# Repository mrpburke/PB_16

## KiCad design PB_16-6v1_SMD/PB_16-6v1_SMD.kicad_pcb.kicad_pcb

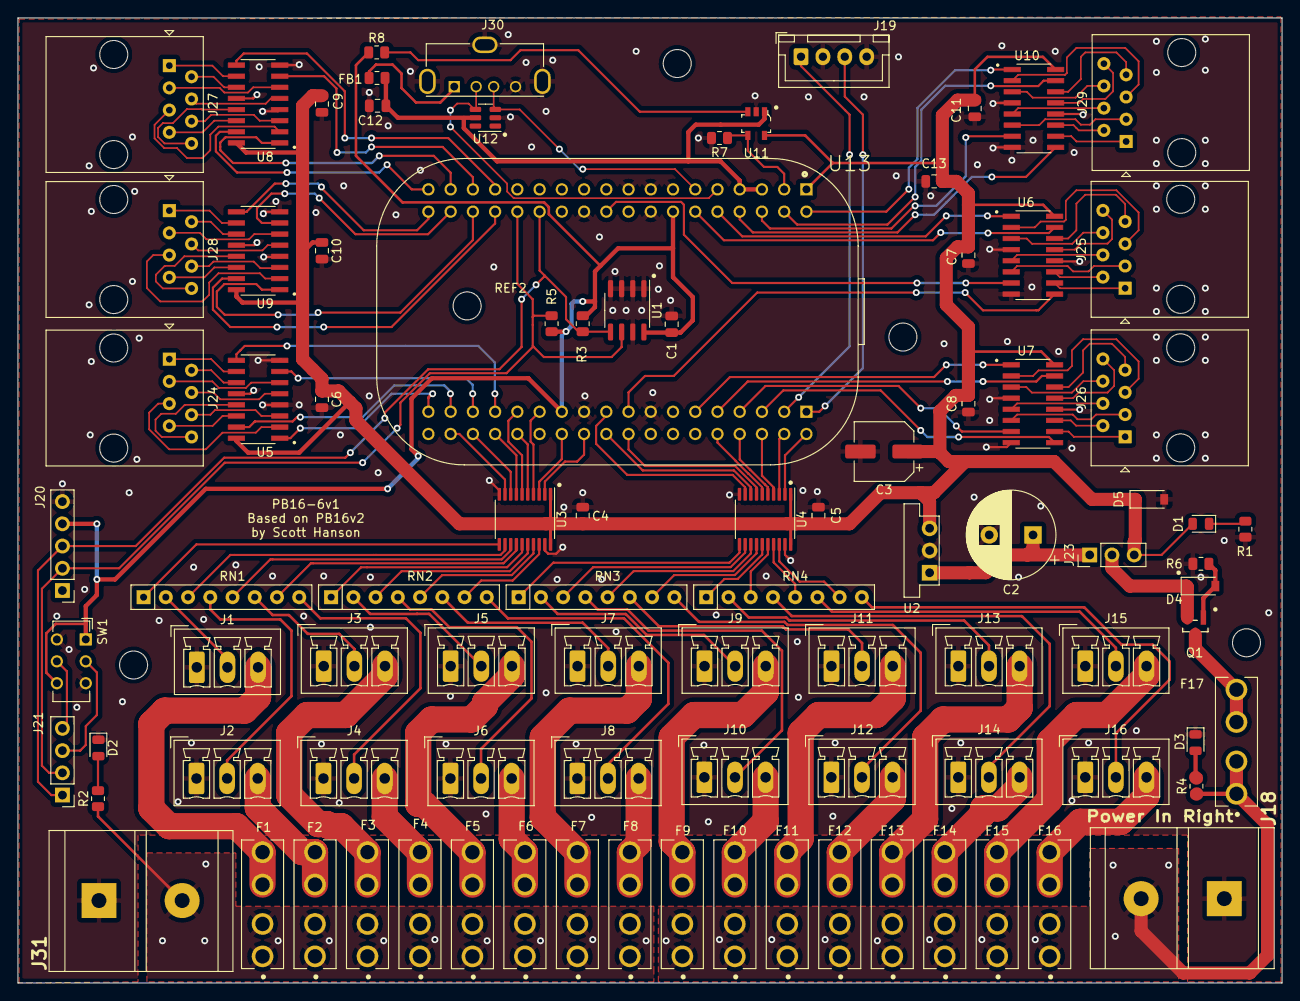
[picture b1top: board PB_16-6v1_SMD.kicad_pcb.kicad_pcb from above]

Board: 2 copper layers, 144.4 x 110.2 mm, 97 parts (0 on the bottom side), 160 nets.

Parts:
C1, C4, C5, C6, C7, C8, C9, C10, C11, C12, C13: 0.1uF; C_0805_2012Metric
C2: 220uF; CP_Radial_D10.0mm_P5.00mm
C3: 100uF; CP_Elec_6.3x5.4_Nichicon
D1: 5V LED; LED_0805_2012Metric
D2: VIN1 LED; LED_0805_2012Metric
D3: VIN2; LED_0805_2012Metric
D4: Zener 10V; D_SOD-123
D5: Zener 5.1V; D_SOD-123
F1, F2, F3, F4, F5, F6, F7, F8, F9, F10, F11, F12, F13, F14, F15, F16, F17: 3544-2; FUSE_3544-2
FB1: 150 OHM; R_0805_2012Metric
J1, J2, J3, J4, J5, J6, J7, J8, J9, J10, J11, J12, J13, J14, J15, J16: PhoenixContact_MCV_1,5_3-G-3.5_1x03_P3.50mm_Vertical
J18: Power In Right; BARRIER_BLOCK_1ROW_2POS_P9.5MM
J19: GPIO Header; JST_XH_B4B-XH-A_1x04_P2.50mm_Vertical
J20: RTC Conn; PinHeader_1x05_P2.54mm_Vertical
J21: OLED Conn; PinHeader_1x04_P2.54mm_Vertical
J23: VIN Voltage; PinHeader_1x03_P2.54mm_Vertical
J24, J25, J26, J27, J28, J29: RJ45; RJ45_Amphenol_54602-x08_Horizontal
J30: USB_A; USB_A_Molex_105057_Vertical
J31: Power In Left; BARRIER_BLOCK_1ROW_2POS_P9.5MM
Q1: DMP3056L-7; Diodes_Inc.-SOT23-01_2017-0-IPC_A
R1: 120; R_0805_2012Metric
R2, R4: 1K; R_0805_2012Metric
R3, R5: 4.7k; R_0805_2012Metric
R6: 100K; R_0805_2012Metric
R7, R8: 10K; R_0805_2012Metric
REF1, REF2, REF3, REF4, REF5: MountingHole_3.2mm_M3
RN1, RN2, RN3, RN4: 33; R_Array_SIP8
SW1: OLED Select; SW_CuK_JS202011CQN_DPDT_Straight
U1: AT24C256C-SSGL-T; SOIC-8_3.9x4.9mm_P1.27mm
U2: OKI-78SR-5_1.5-W36-C; Converter_DCDC_Murata_OKI-78SR_Vertical
U3, U4: SN74HCT245PWR; TSSOP-20_4.4x6.5mm_P0.65mm
U5, U6, U7, U8, U9, U10: AM26C31IDR; SOIC127P600X175-16N
U11: TPS2051BDBVR; SOT-753
U12: TPD4S009DBVR; SOT-23-6
U13: POCKETBEAGLE-SC-569; BEAGLE_POCKETBEAGLE-SC-569

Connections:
+3V3: C1.2, J20.4, R3.1, R5.1, R8.1, SW1.1 (A), SW1.6 (C), U1.8 (VCC), U13.P1_14 (SYS_3.3V), U13.P2_23 (SYS_3.3V)
+5V: C3.1, C4.1, C5.1, C6.1, C7.1, C8.1, C9.1, C10.1, C11.1, C13.1, D1.2 (A), D5.1 (K), J23.3, U2.3 (OUT), U3.1 (DIR), U3.20 (VCC), U4.1 (DIR), U4.20 (VCC), U5.16 (VCC), U6.16 (VCC), U7.16 (VCC), U8.16 (VCC), U9.16 (VCC), U10.16 (VCC), U11.5 (IN), U13.P1_1 (SYS_VIN)
/OLED_Pin_3: J21.3, SW1.2 (B)
/OLED_Pin_4: J21.4, SW1.5 (B)
/Output 1 - 8/DOUT1: J1.2, RN1.2 (R1.2)
/Output 1 - 8/DOUT2: J2.2, RN1.4 (R2.2)
/Output 1 - 8/DOUT3: J3.2, RN1.6 (R3.2)
/Output 1 - 8/DOUT4: J4.2, RN1.8 (R4.2)
/Output 1 - 8/DOUT5: J5.2, RN2.2 (R1.2)
/Output 1 - 8/DOUT6: J6.2, RN2.4 (R2.2)
/Output 1 - 8/DOUT7: J7.2, RN2.6 (R3.2)
/Output 1 - 8/DOUT8: J8.2, RN2.8 (R4.2)
/Output 1 - 8/VOUT1: F1.2_1, F1.2_2, J1.3
/Output 1 - 8/VOUT2: F2.2_1, F2.2_2, J2.3
/Output 1 - 8/VOUT3: F3.2_1, F3.2_2, J3.3
/Output 1 - 8/VOUT4: F4.2_1, F4.2_2, J4.3
/Output 1 - 8/VOUT5: F5.2_1, F5.2_2, J5.3
/Output 1 - 8/VOUT6: F6.2_1, F6.2_2, J6.3
/Output 1 - 8/VOUT7: F7.2_1, F7.2_2, J7.3
/Output 1 - 8/VOUT8: F8.2_1, F8.2_2, J8.3
/Output 9 - 16/DOUT9: J9.2, RN3.2 (R1.2)
/Output 9 - 16/DOUT10: J10.2, RN3.4 (R2.2)
/Output 9 - 16/DOUT11: J11.2, RN3.6 (R3.2)
/Output 9 - 16/DOUT12: J12.2, RN3.8 (R4.2)
/Output 9 - 16/DOUT13: J13.2, RN4.2 (R1.2)
/Output 9 - 16/DOUT14: J14.2, RN4.4 (R2.2)
/Output 9 - 16/DOUT15: J15.2, RN4.6 (R3.2)
/Output 9 - 16/DOUT16: J16.2, RN4.8 (R4.2)
/Output 9 - 16/VOUT9: F9.2_1, F9.2_2, J9.3
/Output 9 - 16/VOUT10: F10.2_1, F10.2_2, J10.3
/Output 9 - 16/VOUT11: F11.2_1, F11.2_2, J11.3
/Output 9 - 16/VOUT12: F12.2_1, F12.2_2, J12.3
/Output 9 - 16/VOUT13: F13.2_1, F13.2_2, J13.3
/Output 9 - 16/VOUT14: F14.2_1, F14.2_2, J14.3
/Output 9 - 16/VOUT15: F15.2_1, F15.2_2, J15.3
/Output 9 - 16/VOUT16: F16.2_1, F16.2_2, J16.3
/USB/V_USB_FB: FB1.2, J30.1 (VBUS)
/VIN_FUSE: F17.2_1, F17.2_2, Q1.3 (D)
DATA1: U3.9 (A8), U13.P2_34 (PRU0_5)
DATA2: U3.8 (A7), U13.P2_32 (PRU0_2)
DATA3: U3.7 (A6), U13.P2_30 (PRU0_3)
DATA4: U3.6 (A5), U13.P2_27 (SPI1_MISO)
DATA5: U3.5 (A4), U13.P2_28 (PRU0_6)
DATA6: U3.4 (A3), U13.P2_25 (SPI1_MOSI)
DATA7: U3.3 (A2), U13.P2_24 (GPIO_48)
DATA8: U3.2 (A1), U13.P2_22 (GPIO_46)
DATA9: U4.9 (A8), U13.P2_19 (GPIO_27)
DATA10: U4.8 (A7), U13.P2_20 (GPIO_64)
DATA11: U4.7 (A6), U13.P2_18 (GPIO_47)
DATA12: U4.6 (A5), U13.P2_10 (GPIO_52)
DATA13: U4.5 (A4), U13.P2_8 (GPIO_60)
DATA14: U4.4 (A3), U13.P2_6 (GPIO_57)
DATA15: U4.3 (A2), U13.P2_4 (GPIO_58)
DATA16: U4.2 (A1), U13.P2_2 (GPIO_59)
GND: C1.1, C2.2, C3.2, C4.2, C5.2, C6.2, C7.2, C8.2, C9.2, C10.2, C11.2, C12.2, C13.2, D2.1 (K), D3.1 (K), D5.2 (A), J1.1, J2.1, J3.1, J4.1, J5.1, J6.1, J7.1, J8.1, J9.1, J10.1, J11.1, J12.1, J13.1, J14.1, J15.1, J16.1, J18.1, J19.2, J19.4, J20.5, J30.4 (GND), J30.5 (Shield), J31.1, R1.2, R6.2, R7.2, SW1.3 (C), SW1.4 (A), U1.1 (A0), U1.2 (A1), U1.3 (A2), U1.4 (GND), U1.7 (WP), U2.2 (GND), U3.10 (GND), U3.19 (~OE), U4.10 (GND), U4.19 (~OE), U5.4 (G), U5.8 (GND), U5.12 (~G), U6.4 (G), U6.8 (GND), U6.12 (~G), U7.4 (G), U7.8 (GND), U7.12 (~G), U8.4 (G), U8.8 (GND), U8.12 (~G), U9.4 (G), U9.8 (GND), U9.12 (~G), U10.4 (G), U10.8 (GND), U10.12 (~G), U11.2 (GND), U12.2 (GND), U13.P1_13 (USB1_ID), U13.P1_15 (USB1_GND), U13.P1_16 (SYS_GND), U13.P1_17 (AIN1.8V_REF-), U13.P1_22 (SYS_GND), U13.P2_15 (SYS_GND), U13.P2_21 (SYS_GND)
GPIO1: J19.1, U13.P2_3 (GPIO_23)
GPIO2: J19.3, U13.P2_1 (PWM1_A)
I2C_SCL: J20.2, J21.2, R5.2, U1.6 (SCL), U13.P1_28 (I2C2_SCL)
I2C_SDA: J20.3, J21.1, R3.2, U1.5 (SDA), U13.P1_26 (I2C2_SDA)
unnamed: C2.1, J23.1, U2.1 (IN)
unnamed: D1.1 (K), R1.1
unnamed: D2.2 (A), R2.2
unnamed: D3.2 (A), R4.2
unnamed: D4.2 (A), Q1.1 (G), R6.1
unnamed: R8.2, U11.3 (~OC)
unnamed: RN1.1 (R1.1), U3.11 (B8)
unnamed: RN1.3 (R2.1), U3.12 (B7)
unnamed: RN1.5 (R3.1), U3.13 (B6)
unnamed: RN1.7 (R4.1), U3.14 (B5)
unnamed: RN2.1 (R1.1), U3.15 (B4)
unnamed: RN2.3 (R2.1), U3.16 (B3)
unnamed: RN2.5 (R3.1), U3.17 (B2)
unnamed: RN2.7 (R4.1), U3.18 (B1)
unnamed: RN3.1 (R1.1), U4.11 (B8)
unnamed: RN3.3 (R2.1), U4.12 (B7)
unnamed: RN3.5 (R3.1), U4.13 (B6)
unnamed: RN3.7 (R4.1), U4.14 (B5)
unnamed: RN4.1 (R1.1), U4.15 (B4)
unnamed: RN4.3 (R2.1), U4.16 (B3)
unnamed: RN4.5 (R3.1), U4.17 (B2)
unnamed: RN4.7 (R4.1), U4.18 (B1)
OUT17: U7.9 (3A), U13.P2_5 (UART4_RX)
OUT17+: J26.1, U7.10 (3Y)
OUT17-: J26.2, U7.11 (3Z)
OUT18: U7.7 (2A), U13.P2_7 (UART4_TX)
OUT18+: J26.3, U7.6 (2Y)
OUT18-: J26.4, U7.5 (2Z)
OUT19: U7.1 (1A), U13.P2_11 (I2C1_SDA)
OUT19+: J26.5, U7.2 (1Y)
OUT19-: J26.6, U7.3 (1Z)
OUT20: U7.15 (4A), U13.P2_9 (I2C1_SCL)
OUT20+: J26.7, U7.14 (4Y)
OUT20-: J26.8, U7.13 (4Z)
OUT21: U5.9 (3A), U13.P2_29 (SPI1_CLK)
OUT21+: J24.1, U5.10 (3Y)
OUT21-: J24.2, U5.11 (3Z)
OUT22: U5.7 (2A), U13.P2_31 (SPI1_CS)
OUT22+: J24.3, U5.6 (2Y)
OUT22-: J24.4, U5.5 (2Z)
OUT23: U5.1 (1A), U13.P2_35 (AIN5/GPIO86)
OUT23+: J24.5, U5.2 (1Y)
OUT23-: J24.6, U5.3 (1Z)
OUT24: U5.15 (4A), U13.P2_33 (GPIO_45)
OUT24+: J24.7, U5.14 (4Y)
OUT24-: J24.8, U5.13 (4Z)
OUT25: U6.9 (3A), U13.P2_17 (GPIO_65)
OUT25+: J25.1, U6.10 (3Y)
OUT25-: J25.2, U6.11 (3Z)
OUT26: U6.7 (2A), U13.P1_20 (GPIO_20)
OUT26+: J25.3, U6.6 (2Y)
OUT26-: J25.4, U6.5 (2Z)
OUT27: U6.1 (1A), U13.P1_10 (SPI0_MISO)
OUT27+: J25.5, U6.2 (1Y)
OUT27-: J25.6, U6.3 (1Z)
OUT28: U6.15 (4A), U13.P1_12 (SPI0_MOSI)
OUT28+: J25.7, U6.14 (4Y)
OUT28-: J25.8, U6.13 (4Z)
OUT29: U8.9 (3A), U13.P1_29 (PRU0_7)
OUT29+: J27.1, U8.10 (3Y)
OUT29-: J27.2, U8.11 (3Z)
OUT30: U8.7 (2A), U13.P1_31 (PRU0_4)
OUT30+: J27.3, U8.6 (2Y)
OUT30-: J27.4, U8.5 (2Z)
OUT31: U8.1 (1A), U13.P1_33 (PRU0_1)
OUT31+: J27.5, U8.2 (1Y)
OUT31-: J27.6, U8.3 (1Z)
OUT32: U8.15 (4A), U13.P1_35 (PRU1_10)
OUT32+: J27.7, U8.14 (4Y)
OUT32-: J27.8, U8.13 (4Z)
OUT33: U9.9 (3A), U13.P1_36 (PWM0_A)
OUT33+: J28.1, U9.10 (3Y)
OUT33-: J28.2, U9.11 (3Z)
OUT34: U9.7 (2A), U13.P1_34 (GPIO_26)
OUT34+: J28.3, U9.6 (2Y)
OUT34-: J28.4, U9.5 (2Z)
OUT35: U9.1 (1A), U13.P1_32 (UART0_RX)
OUT35+: J28.5, U9.2 (1Y)
OUT35-: J28.6, U9.3 (1Z)
OUT36: U9.15 (4A), U13.P1_30 (UART0_TX)
OUT36+: J28.7, U9.14 (4Y)
OUT36-: J28.8, U9.13 (4Z)
OUT37: U10.9 (3A), U13.P1_8 (SPI0_CLK)
OUT37+: J29.1, U10.10 (3Y)
OUT37-: J29.2, U10.11 (3Z)
OUT38: U10.7 (2A), U13.P1_6 (SPI0_CS)
OUT38+: J29.3, U10.6 (2Y)
OUT38-: J29.4, U10.5 (2Z)
OUT39: U10.1 (1A), U13.P1_2 (AIN6/GPIO87)
OUT39+: J29.5, U10.2 (1Y)
OUT39-: J29.6, U10.3 (1Z)
OUT40: U10.15 (4A), U13.P1_4 (GPIO_89)
OUT40+: J29.7, U10.14 (4Y)
OUT40-: J29.8, U10.13 (4Z)
USB_D+: J30.3 (D+), U12.3 (D2+), U13.P1_11 (USB1_DP)
USB_D-: J30.2 (D-), U12.4 (D2-), U13.P1_9 (USB1_DN)
USB_DVBUS: R7.1, U11.4 (~EN), U13.P1_3 (USB1_DRVVBUS)
VCC: D4.1 (K), J23.2, Q1.2 (S)
VIN1: F1.1_1, F1.1_2, F2.1_1, F2.1_2, F3.1_1, F3.1_2, F4.1_1, F4.1_2, F5.1_1, F5.1_2, F6.1_1, F6.1_2, F7.1_1, F7.1_2, F8.1_1, F8.1_2, J31.2, R2.1
VIN2: F9.1_1, F9.1_2, F10.1_1, F10.1_2, F11.1_1, F11.1_2, F12.1_1, F12.1_2, F13.1_1, F13.1_2, F14.1_1, F14.1_2, F15.1_1, F15.1_2, F16.1_1, F16.1_2, F17.1_1, F17.1_2, J18.2, R4.1
V_USB: C12.1, FB1.1, U11.1 (OUT), U12.5 (VCC), U13.P1_5 (USB1_VBUS), U13.P1_7 (USB1_VIN)

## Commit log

2022-05-09 Added PB16-6v1
2022-05-09 Add PB16-6v1
